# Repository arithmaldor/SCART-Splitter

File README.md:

# SCART-Splitter
This is a simple SCART splitter based on the THS7374.
The circuit is is AC-bias mode so component video will be properly driven. It can be easily adapted for a variety of connectors; RCA, BNC, VGA, whatever you need.
Audio is simply connected to both outputs so might be a bit quiet.

# Thanks
This was loosely based on Voultar's open source [Dual Output board.](https://oshpark.com/shared_projects/6o0jvLnD)
Special thanks also to RetroRGB; thanks to examining the 2DVI boards I gained a better understanding of these circuits.

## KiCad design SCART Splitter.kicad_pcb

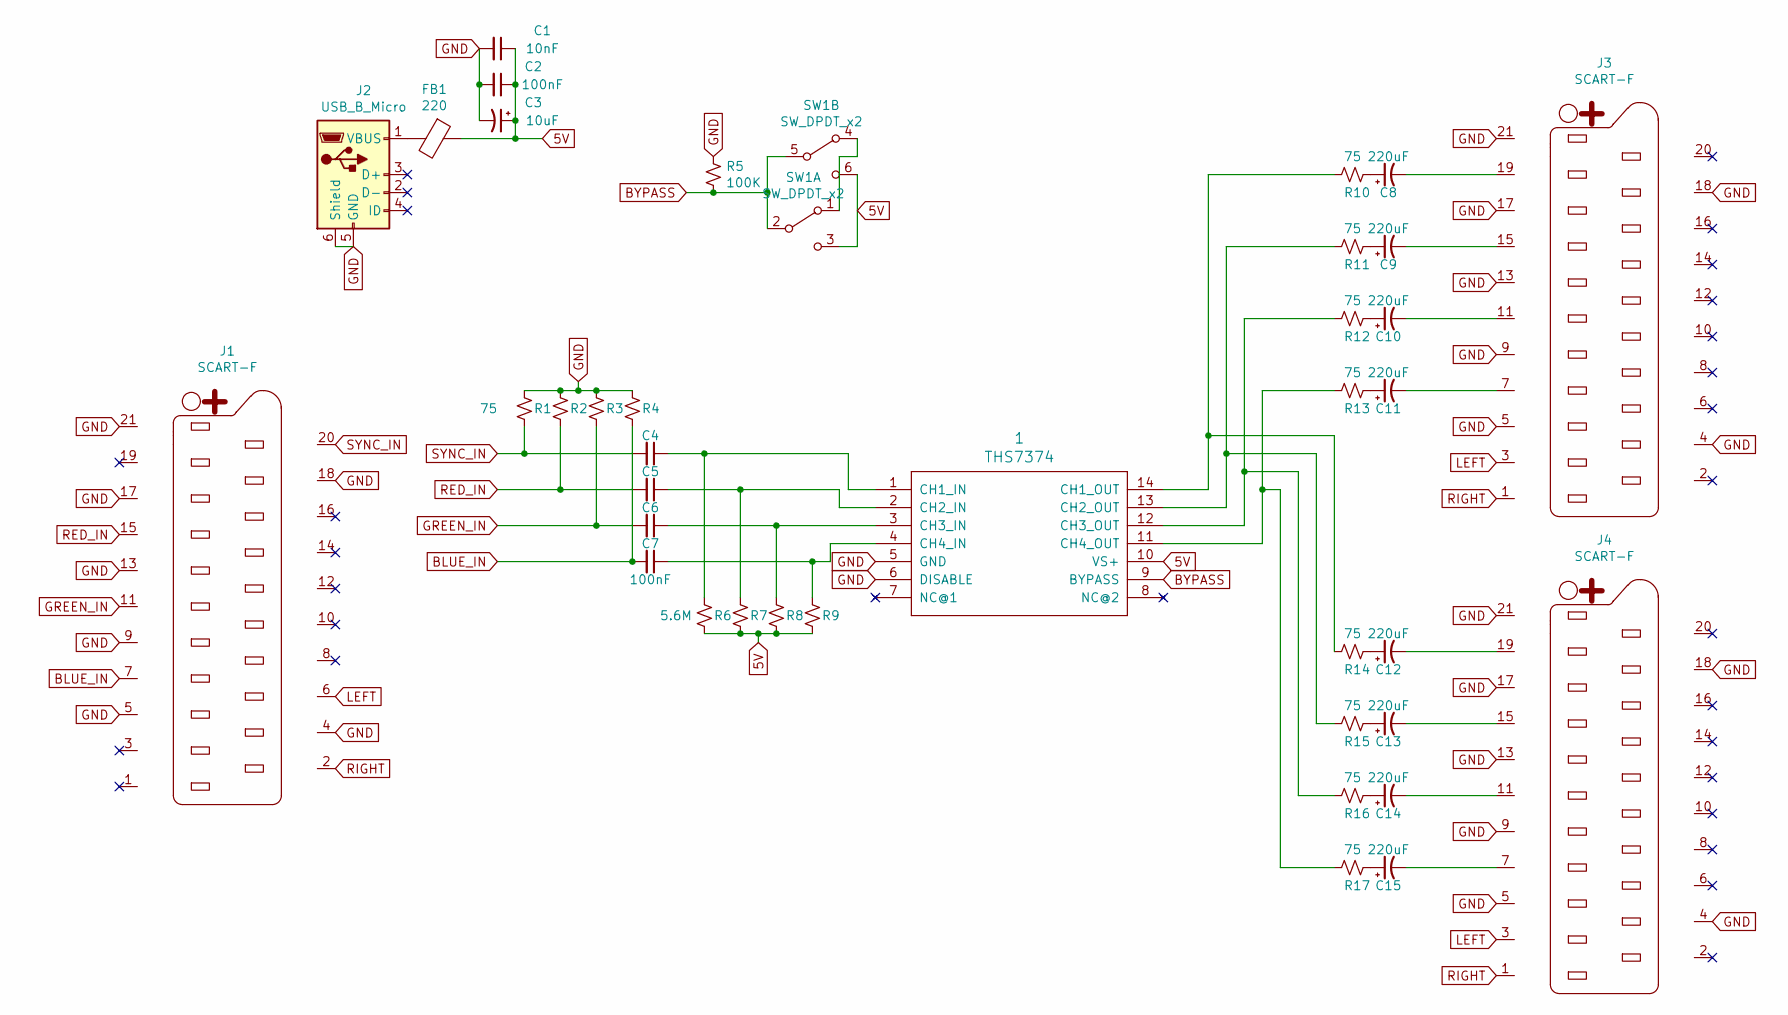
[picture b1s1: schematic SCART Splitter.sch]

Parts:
1: THS7374; TSSOP-14_4.4x5mm_P0.65mm
C1: 10nF; C_0603_1608Metric_Pad1.05x0.95mm_HandSolder
C2, C4, C5, C6, C7: 100nF; C_0603_1608Metric_Pad1.05x0.95mm_HandSolder
C3: 10uF; CP_Elec_4x5.4
C8, C9, C10, C11, C12, C13, C14, C15: 220uF; CP_Elec_8x10
FB1: 220; L_0603_1608Metric_Pad1.05x0.95mm_HandSolder
J1, J3, J4: SCART-F
J2: USB_B_Micro; USB_Micro-B_Molex-105017-0001
R1, R2, R3, R4, R10, R11, R12, R13, R14, R15, R16, R17: 75; R_0603_1608Metric_Pad1.05x0.95mm_HandSolder
R5: 100K; R_0603_1608Metric_Pad1.05x0.95mm_HandSolder
R6, R7, R8, R9: 5.6M; R_0603_1608Metric_Pad1.05x0.95mm_HandSolder
SW1: SW_DPDT_x2; JS202011

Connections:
5V: 1.10 (VS+), C1.1, C2.1, C3.1, FB1.1, R6.2, R7.2, R8.2, R9.2, SW1.3 (C), SW1.6 (C); also elsewhere on the board
BLUE_IN: C7.2, J1.7, R4.2
BYPASS: 1.9 (BYPASS), R5.2, SW1.2 (B), SW1.5 (B); also elsewhere on the board
GND: 1.5 (GND), 1.6 (DISABLE), C1.2, C2.2, C3.2, J1.4, J1.5, J1.9, J1.13, J1.17, J1.18, J1.21, J2.5 (GND), J2.6 (Shield), J3.4, J3.5, J3.9, J3.13, J3.17, J3.18, J3.21, J4.4, J4.5, J4.9, J4.13, J4.17, J4.18, J4.21, R1.1, R2.1, R3.1, R4.1, R5.1; also elsewhere on the board
GREEN_IN: C6.2, J1.11, R3.2
LEFT: J1.6, J3.3, J4.3
unnamed 6: 1.1 (CH1_IN), C4.1, R6.1; also elsewhere on the board
unnamed 7: 1.2 (CH2_IN), C5.1, R7.1; also elsewhere on the board
unnamed 8: 1.3 (CH3_IN), C6.1, R8.1; also elsewhere on the board
unnamed 9: 1.4 (CH4_IN), C7.1, R9.1; also elsewhere on the board
unnamed 12: 1.11 (CH4_OUT), R13.2, R17.2; also elsewhere on the board
unnamed 13: 1.12 (CH3_OUT), R12.2, R16.2; also elsewhere on the board
unnamed 14: 1.13 (CH2_OUT), R11.2, R15.2; also elsewhere on the board
unnamed 15: 1.14 (CH1_OUT), R10.2, R14.2; also elsewhere on the board
unnamed: C8.1, R10.1
unnamed: C8.2, J3.19
unnamed: C9.1, R11.1
unnamed: C9.2, J3.15
unnamed: C10.1, R12.1
unnamed: C10.2, J3.11
unnamed: C11.1, R13.1
unnamed: C11.2, J3.7
unnamed: C12.1, R14.1
unnamed: C12.2, J4.19
unnamed: C13.1, R15.1
unnamed: C13.2, J4.15
unnamed: C14.1, R16.1
unnamed: C14.2, J4.11
unnamed: C15.1, R17.1
unnamed: C15.2, J4.7
unnamed: FB1.2, J2.1 (VBUS)
unnamed: SW1.1 (A), SW1.4 (A)
RED_IN: C5.2, J1.15, R2.2
RIGHT: J1.2, J3.1, J4.1
SYNC_IN: C4.2, J1.20, R1.2

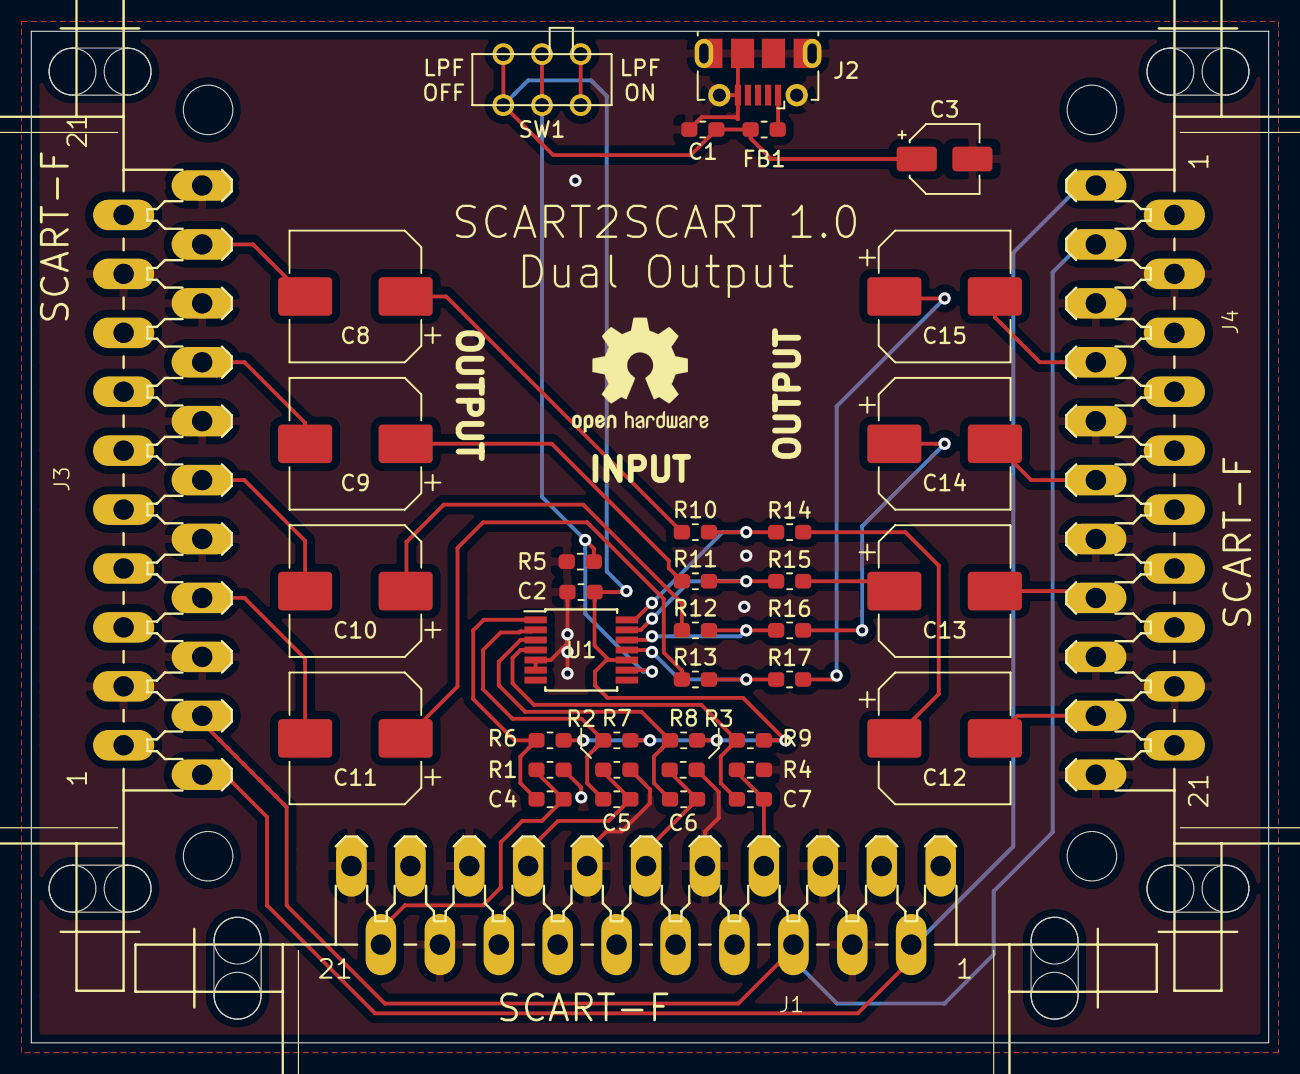
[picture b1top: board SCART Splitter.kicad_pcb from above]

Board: 2 copper layers, 80.0 x 65.4 mm, 39 parts (0 on the bottom side), 35 nets.

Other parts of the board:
U1: THS7374; TSSOP-14_4.4x5mm_P0.65mm

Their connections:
5V: U1.10; also elsewhere on the board
BYPASS: U1.9; also elsewhere on the board
GND: U1.5, U1.6; also elsewhere on the board
unnamed 6: U1.1; also elsewhere on the board
unnamed 7: U1.2; also elsewhere on the board
unnamed 8: U1.3; also elsewhere on the board
unnamed 9: U1.4; also elsewhere on the board
unnamed 12: U1.11; also elsewhere on the board
unnamed 13: U1.12; also elsewhere on the board
unnamed 14: U1.13; also elsewhere on the board
unnamed 15: U1.14; also elsewhere on the board

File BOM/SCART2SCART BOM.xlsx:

Qty | Ref(s) | Value | Footprint | Description | Note | Digikey | Arrow | LCSC | Other
1 | C1 | 10nF | 0603 | Ceramic 50V |  | https://www.digikey.com/product-detail/en/samsung-electro-me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 | https://www.arrow.com/en/products/cc0603krx7r9bb103/yageo | https://lcsc.com/product-detail/Others_Samsung-Electro-Mecha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
5 | C2, C4-7 | 100nF | 0603 | Ceramic 50V |  | https://www.digikey.com/product-detail/en/CL10F104ZO8NNNC/12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 | https://www.arrow.com/en/products/cl10f104zo8nnnc/samsung-el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 | https://lcsc.com/product-detail/Multilayer-Ceramic-Capacitor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
1 | C3 | 10uF | 4x5.4 | Elec. 25V |  | https://www.digikey.com/product-detail/en/panasonic-electron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 | https://www.arrow.com/en/products/eeefk1e100r/panasonic | https://lcsc.com/product-detail/Others_PANASONIC-EEE1EA100WA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
8 | C8-15 | 220uF | 8x10 | Elec. 25V |  | https://www.digikey.com/product-detail/en/nichicon/UUD1E221M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 | https://www.arrow.com/en/products/uud1e221mnl1gs/nichicon | https://lcsc.com/product-detail/Others_Nichicon_UCD1E221MCL1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
12 | R1-4, 10-17 | 75R | 0603 | 0.01 |  | https://www.digikey.com/product-detail/en/rohm-semiconductor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 | https://www.arrow.com/en/products/erj-3ekf75r0v/panasonic | https://lcsc.com/product-detail/Chip-Resistor-Surface-Mount_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
1 | R5 | 100K | 0603 | 0.01 |  | https://www.digikey.com/product-detail/en/yageo/RC0603FR-071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 | https://www.arrow.com/en/products/erj-3ekf1003v/panasonic | https://lcsc.com/product-detail/Chip-Resistor-Surface-Mount_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
4 | R6-9 | 5.6M | 0603 | 0.01 |  | https://www.digikey.com/product-detail/en/vishay-dale/CRCW06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 | https://www.arrow.com/en/products/crcw06035m60fkea/vishay | https://lcsc.com/product-detail/Chip-Resistor-Surface-Mount_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
1 | FB1 | 220R | 0603 | Ferrite Bead |  | https://www.digikey.com/product-detail/en/tdk-corporation/MP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 | https://www.arrow.com/en/products/mpz1608s221ata00/tdk | https://lcsc.com/product-detail/Ferrite-Beads-And-Chips_TDK_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
1 | U1 | THS7374 | TSSOP-14 |  |  | https://www.digikey.com/product-detail/en/texas-instruments/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 | https://www.arrow.com/en/products/ths7374ipw/texas-instruments |  | https://console5.com/store/ths7374-4-channel-sdtv-hdtv-video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
3 | J1, 3, 4 | SCART | Right Angle |  |  |  |  |  | https://console5.com/store/female-scart-jp21-through-hole-pc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
1 | J2 | microUSB | Right Angle | Molex Style |  | https://www.digikey.com/product-detail/en/molex/1050170001/W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 | https://www.arrow.com/en/products/1050170001/molex | https://lcsc.com/product-detail/USB-Connectors_Jing-Extensio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
1 | SW1 | DPDT | THT RA |  |  | https://www.digikey.com/product-detail/en/c-k/JS202011AQN/40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 | https://www.arrow.com/en/products/js202011aqn/ck | https://lcsc.com/product-detail/Toggle-Switches_C-K_JS202011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

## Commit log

2020-07-11 Created a simple case.
    I've created a simple case to protect the PCB. The shop I had laser cut it for me wanted me to confirm the dimensions, so I've included a file showing them. They used the PDF, but the SVG should work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

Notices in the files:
SCART Splitter.kicad_pcb:
Licensed under CERN OHL 1.2
